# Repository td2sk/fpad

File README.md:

# fpad KiCAD data

## Features

- Key switch (Cherry MX compatible) x16
- Rotary Encoder - Illuminated (RGB) x5
- JoyStick x1
- Display
- QMK Firmware (TODO)

## License

- MIT License

## Files

- fpad7.kicad_pcb: main board
- fpad_bottom.kicad_pcb: bottom plate
- fpad_top.kicad_pcb: top plate

## Versions

- latest (recommended)
  - in root directory
- rev1 (deprecated)
  - in [releases/rev1](releases/rev1)
  - [errata](releases/rev1/errata.md)

## BOM

| Component                             | Label        | LCSC     | remarks                                                     |
| ------------------------------------- | ------------ | -------- | ----------------------------------------------------------- |
| Capacitor 0.1u 0402                   | C1           | C307331  |                                                             |
| 1N4148WS Diode SOD-323 x 16           | D1 ~ D16     | C2128    |                                                             |
| SK6812MINI-E LED x 16                 | LED1 ~ LED16 | C5149201 |                                                             |
| SSD1306 OLED Display                  | OL1          |          |                                                             |
| Register 7.5kΩ 0402                   | R1           | C25918   |                                                             |
| Register 100kΩ 3216                   | R2           | C17900   |                                                             |
| Register 10kΩ 0402 x2                 | R3, R4       | C25744   |                                                             |
| Register 3.3kΩ 0402 x2                | R5, R6       | C25890   |                                                             |
| Rotary Encoder - Illuminated (RGB) x5 | S1 ~ S5      |          | https://www.sparkfun.com/products/15141                     |
| RKJXV122400R JoyStick                 | S6           |          | https://tech.alpsalpine.com/j/products/detail/RKJXV122400R/ |
| Kailh Switch Socket x16               | SW1 ~ SW16   | C2803348 | CherryMX Compatible                                         |
| Tactile Switch                        | SW17         |          | reset button for ProMicro                                   |
| Arduino ProMicro                      | U1           |          |                                                             |
| XL9555 I/O Expander                   | U2           | C609791  |                                                             |
| IS31FL3208A LED Driver                | U3           | C2940551 |                                                             |

## Issues

- [rev1/errata.md](releases/rev1/errata.md)

## External files

### 3D CONTENTCENTRAL

The following 3D models are obtained from [3D CONTENTCENTRAL](https://www.3dcontentcentral.com/).
They are not included in this repository due to license, so please obtain them on your own and place them in the following paths.

- [Keycap](https://www.3dcontentcentral.com/secure/download-model.aspx?catalogid=171&id=941483)
  - external/3dcontentcentral/Mx_Keycap.step
- [JoyStick](https://www.3dcontentcentral.com/secure/download-model.aspx?catalogid=171&id=1681961)
  - external/3dcontentcentral/User Library-RKJXV122400R.step
- [RotaryEncoder](https://www.3dcontentcentral.com/download-model.aspx?catalogid=171&id=630216)
  - external/3dcontentcentral/User Library-Rotary Encoder v21.STEP

### SnapEDA

SnapEDA files are provided under this license as described in the following [FAQ - SnapEDA](https://www.snapeda.com/about/FAQ/).

### kbd, SparkFun-KiCAD-Libraries

Comply with the original license

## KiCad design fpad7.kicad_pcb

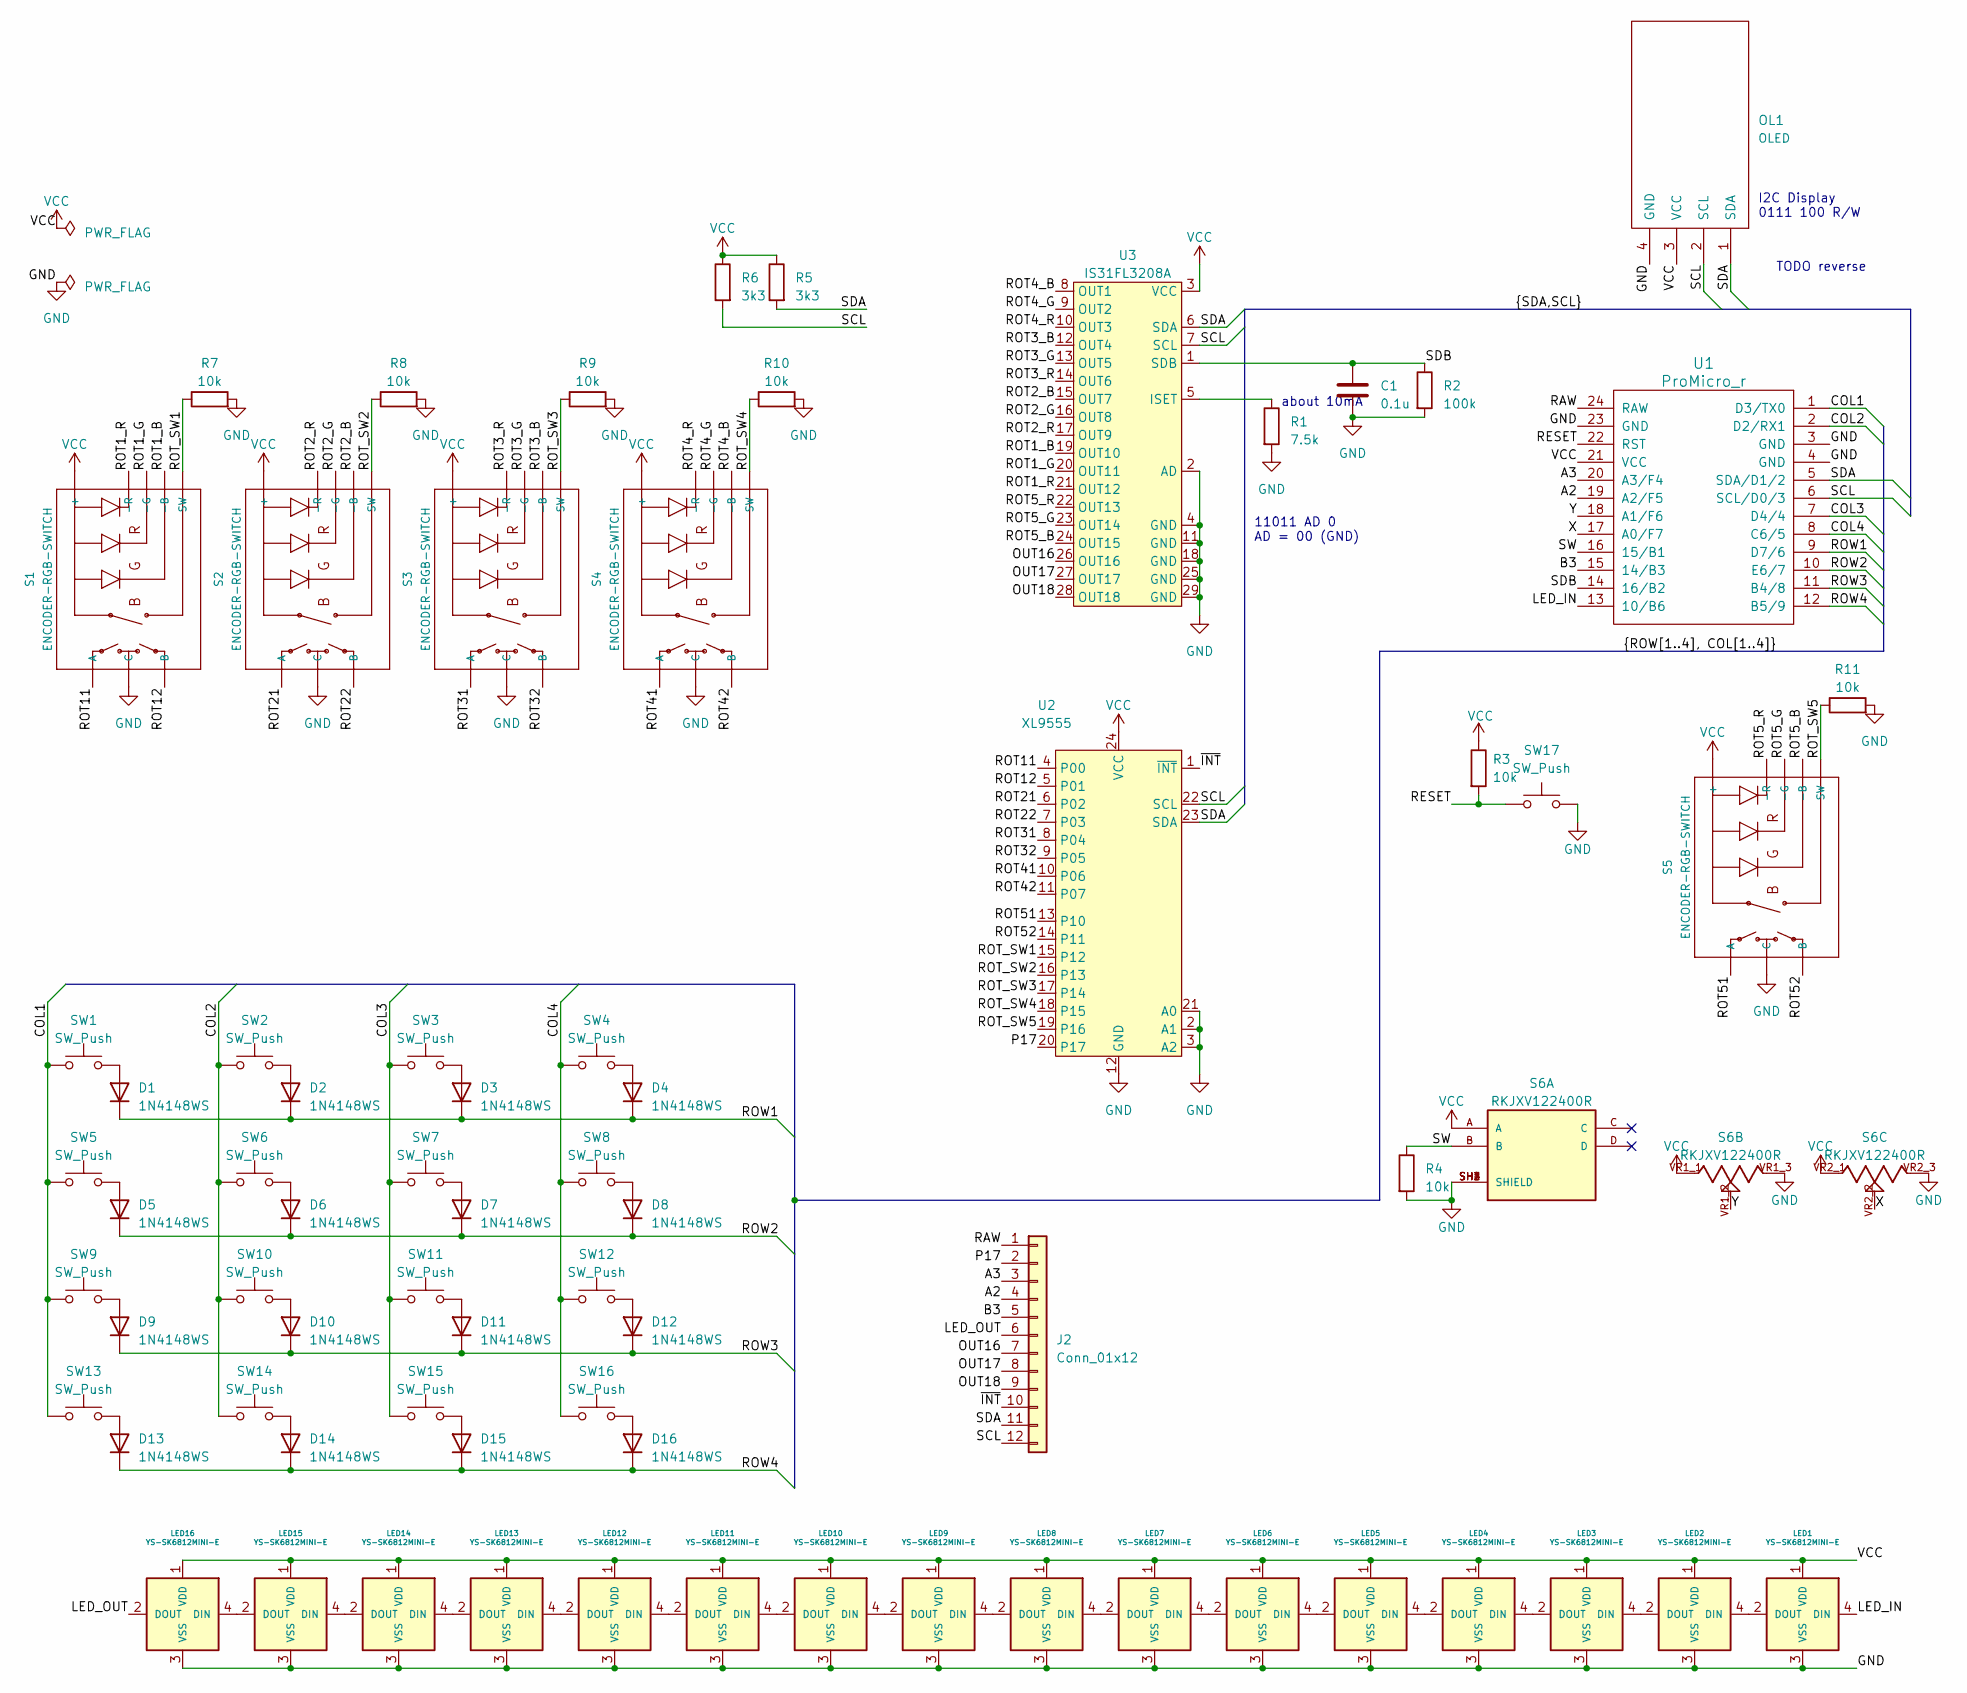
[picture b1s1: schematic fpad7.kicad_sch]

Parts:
C1: 0.1u; C_0402_1005Metric; LCSC C307331
D1, D2, D3, D4, D5, D6, D7, D8, D9, D10, D11, D12, D13, D14, D15, D16: 1N4148WS; D_SOD-323; LCSC C2128
J2: Conn_01x12; PinHeader_1x12_P1.27mm_Vertical
LED1, LED2, LED3, LED4, LED5, LED6, LED7, LED8, LED9, LED10, LED11, LED12, LED13, LED14, LED15, LED16: YS-SK6812MINI-E
OL1: OLED; OLED_v2
R1: 7.5k; R_0402_1005Metric; LCSC C25918
R2: 100k; R_1206_3216Metric; LCSC C17900
R3, R4, R7, R8, R9, R10, R11: 10k; R_0402_1005Metric; LCSC C25744
R5, R6: 3k3; R_0402_1005Metric; LCSC C25890
S1, S2, S3, S4, S5: ENCODER-RGB-SWITCH; ENCODER_LED_3
S6: RKJXV122400R; SW_RKJXV122400R; PARTREV N/A
SW1, SW2, SW3, SW4, SW5, SW6, SW7, SW8, SW9, SW10, SW11, SW12, SW13, SW14, SW15, SW16: SW_Push; CherryMX_Hotswap
SW17: SW_Push; SW_PUSH_6mm_H5mm
U1: ProMicro_r; ProMicro_v3
U2: XL9555; SSOP-24_5.3x8.2mm_P0.65mm; LCSC C609791
U3: IS31FL3208A; QFN-28-1EP_4x4mm_P0.4mm_EP2.4x2.4mm; LCSC C2940551

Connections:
/A2: J2.4, U1.19 (A2/F5)
/A3: J2.3, U1.20 (A3/F4)
/B3: J2.5, U1.15 (14/B3)
/COL1: SW1.1, SW5.1, SW9.1, SW13.1, U1.1 (D3/TX0)
/COL2: SW2.1, SW6.1, SW10.1, SW14.1, U1.2 (D2/RX1)
/COL3: SW3.1, SW7.1, SW11.1, SW15.1, U1.7 (D4/4)
/COL4: SW4.1, SW8.1, SW12.1, SW16.1, U1.8 (C6/5)
/LED_IN: LED1.4 (DIN), U1.13 (10/B6)
/LED_OUT: J2.6, LED16.2 (DOUT)
/OUT16: J2.7, U3.26 (OUT16)
/OUT17: J2.8, U3.27 (OUT17)
/OUT18: J2.9, U3.28 (OUT18)
/P17: J2.2, U2.20 (P17)
/RAW: J2.1, U1.24 (RAW)
/RESET: R3.2, SW17.1, U1.22 (RST)
/ROT1_B: S1.4 (-B), U3.19 (OUT10)
/ROT1_G: S1.2 (-G), U3.20 (OUT11)
/ROT1_R: S1.1 (-R), U3.21 (OUT12)
/ROT2_B: S2.4 (-B), U3.15 (OUT7)
/ROT2_G: S2.2 (-G), U3.16 (OUT8)
/ROT2_R: S2.1 (-R), U3.17 (OUT9)
/ROT3_B: S3.4 (-B), U3.12 (OUT4)
/ROT3_G: S3.2 (-G), U3.13 (OUT5)
/ROT3_R: S3.1 (-R), U3.14 (OUT6)
/ROT4_B: S4.4 (-B), U3.8 (OUT1)
/ROT4_G: S4.2 (-G), U3.9 (OUT2)
/ROT4_R: S4.1 (-R), U3.10 (OUT3)
/ROT5_B: S5.4 (-B), U3.24 (OUT15)
/ROT5_G: S5.2 (-G), U3.23 (OUT14)
/ROT5_R: S5.1 (-R), U3.22 (OUT13)
/ROT11: S1.A, U2.4 (P00)
/ROT12: S1.B, U2.5 (P01)
/ROT21: S2.A, U2.6 (P02)
/ROT22: S2.B, U2.7 (P03)
/ROT31: S3.A, U2.8 (P04)
/ROT32: S3.B, U2.9 (P05)
/ROT41: S4.A, U2.10 (P06)
/ROT42: S4.B, U2.11 (P07)
/ROT51: S5.A, U2.13 (P10)
/ROT52: S5.B, U2.14 (P11)
/ROT_SW1: R7.1, S1.3 (SW), U2.15 (P12)
/ROT_SW2: R8.1, S2.3 (SW), U2.16 (P13)
/ROT_SW3: R9.1, S3.3 (SW), U2.17 (P14)
/ROT_SW4: R10.1, S4.3 (SW), U2.18 (P15)
/ROT_SW5: R11.1, S5.3 (SW), U2.19 (P16)
/ROW1: D1.1 (K), D2.1 (K), D3.1 (K), D4.1 (K), U1.9 (D7/6)
/ROW2: D5.1 (K), D6.1 (K), D7.1 (K), D8.1 (K), U1.10 (E6/7)
/ROW3: D9.1 (K), D10.1 (K), D11.1 (K), D12.1 (K), U1.11 (B4/8)
/ROW4: D13.1 (K), D14.1 (K), D15.1 (K), D16.1 (K), U1.12 (B5/9)
/SCL: J2.12, OL1.2 (SCL), R6.2, U1.6 (SCL/D0/3), U2.22 (SCL), U3.7 (SCL)
/SDA: J2.11, OL1.1 (SDA), R5.2, U1.5 (SDA/D1/2), U2.23 (SDA), U3.6 (SDA)
/SDB: C1.1, R2.1, U1.14 (16/B2), U3.1 (SDB)
/SW: R4.1, S6.B, U1.16 (15/B1)
/X: S6.VR2_2, U1.17 (A0/F7)
/Y: S6.VR1_2, U1.18 (A1/F6)
/~INT: J2.10, U2.1 (~INT)
GND: C1.2, LED1.3 (VSS), LED2.3 (VSS), LED3.3 (VSS), LED4.3 (VSS), LED5.3 (VSS), LED6.3 (VSS), LED7.3 (VSS), LED8.3 (VSS), LED9.3 (VSS), LED10.3 (VSS), LED11.3 (VSS), LED12.3 (VSS), LED13.3 (VSS), LED14.3 (VSS), LED15.3 (VSS), LED16.3 (VSS), OL1.4 (GND), R1.2, R2.2, R4.2, R7.2, R8.2, R9.2, R10.2, R11.2, S1.C, S2.C, S3.C, S4.C, S5.C, S6.SH1 (SHIELD), S6.SH2 (SHIELD), S6.SH3 (SHIELD), S6.SH4 (SHIELD), S6.VR1_3, S6.VR2_3, SW17.2, U1.3 (GND), U1.4 (GND), U1.23 (GND), U2.2 (A1), U2.3 (A2), U2.12 (GND), U2.21 (A0), U3.2 (AD), U3.4 (GND), U3.11 (GND), U3.18 (GND), U3.25 (GND), U3.29 (GND)
unnamed: D1.2 (A), SW1.2
unnamed: D2.2 (A), SW2.2
unnamed: D3.2 (A), SW3.2
unnamed: D4.2 (A), SW4.2
unnamed: D5.2 (A), SW5.2
unnamed: D6.2 (A), SW6.2
unnamed: D7.2 (A), SW7.2
unnamed: D8.2 (A), SW8.2
unnamed: D9.2 (A), SW9.2
unnamed: D10.2 (A), SW10.2
unnamed: D11.2 (A), SW11.2
unnamed: D12.2 (A), SW12.2
unnamed: D13.2 (A), SW13.2
unnamed: D14.2 (A), SW14.2
unnamed: D15.2 (A), SW15.2
unnamed: D16.2 (A), SW16.2
unnamed: LED1.2 (DOUT), LED2.4 (DIN)
unnamed: LED2.2 (DOUT), LED3.4 (DIN)
unnamed: LED3.2 (DOUT), LED4.4 (DIN)
unnamed: LED4.2 (DOUT), LED5.4 (DIN)
unnamed: LED5.2 (DOUT), LED6.4 (DIN)
unnamed: LED6.2 (DOUT), LED7.4 (DIN)
unnamed: LED7.2 (DOUT), LED8.4 (DIN)
unnamed: LED8.2 (DOUT), LED9.4 (DIN)
unnamed: LED9.2 (DOUT), LED10.4 (DIN)
unnamed: LED10.2 (DOUT), LED11.4 (DIN)
unnamed: LED11.2 (DOUT), LED12.4 (DIN)
unnamed: LED12.2 (DOUT), LED13.4 (DIN)
unnamed: LED13.2 (DOUT), LED14.4 (DIN)
unnamed: LED14.2 (DOUT), LED15.4 (DIN)
unnamed: LED15.2 (DOUT), LED16.4 (DIN)
unnamed: R1.1, U3.5 (ISET)
VCC: LED1.1 (VDD), LED2.1 (VDD), LED3.1 (VDD), LED4.1 (VDD), LED5.1 (VDD), LED6.1 (VDD), LED7.1 (VDD), LED8.1 (VDD), LED9.1 (VDD), LED10.1 (VDD), LED11.1 (VDD), LED12.1 (VDD), LED13.1 (VDD), LED14.1 (VDD), LED15.1 (VDD), LED16.1 (VDD), OL1.3 (VCC), R3.1, R5.1, R6.1, S1.5 (+), S2.5 (+), S3.5 (+), S4.5 (+), S5.5 (+), S6.A, S6.VR1_1, S6.VR2_1, U1.21 (VCC), U2.24 (VCC), U3.3 (VCC)

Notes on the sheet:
TODO reverse
about 10mA
I2C Display 0111 100 R/W
11011 AD 0 AD = 00 (GND)

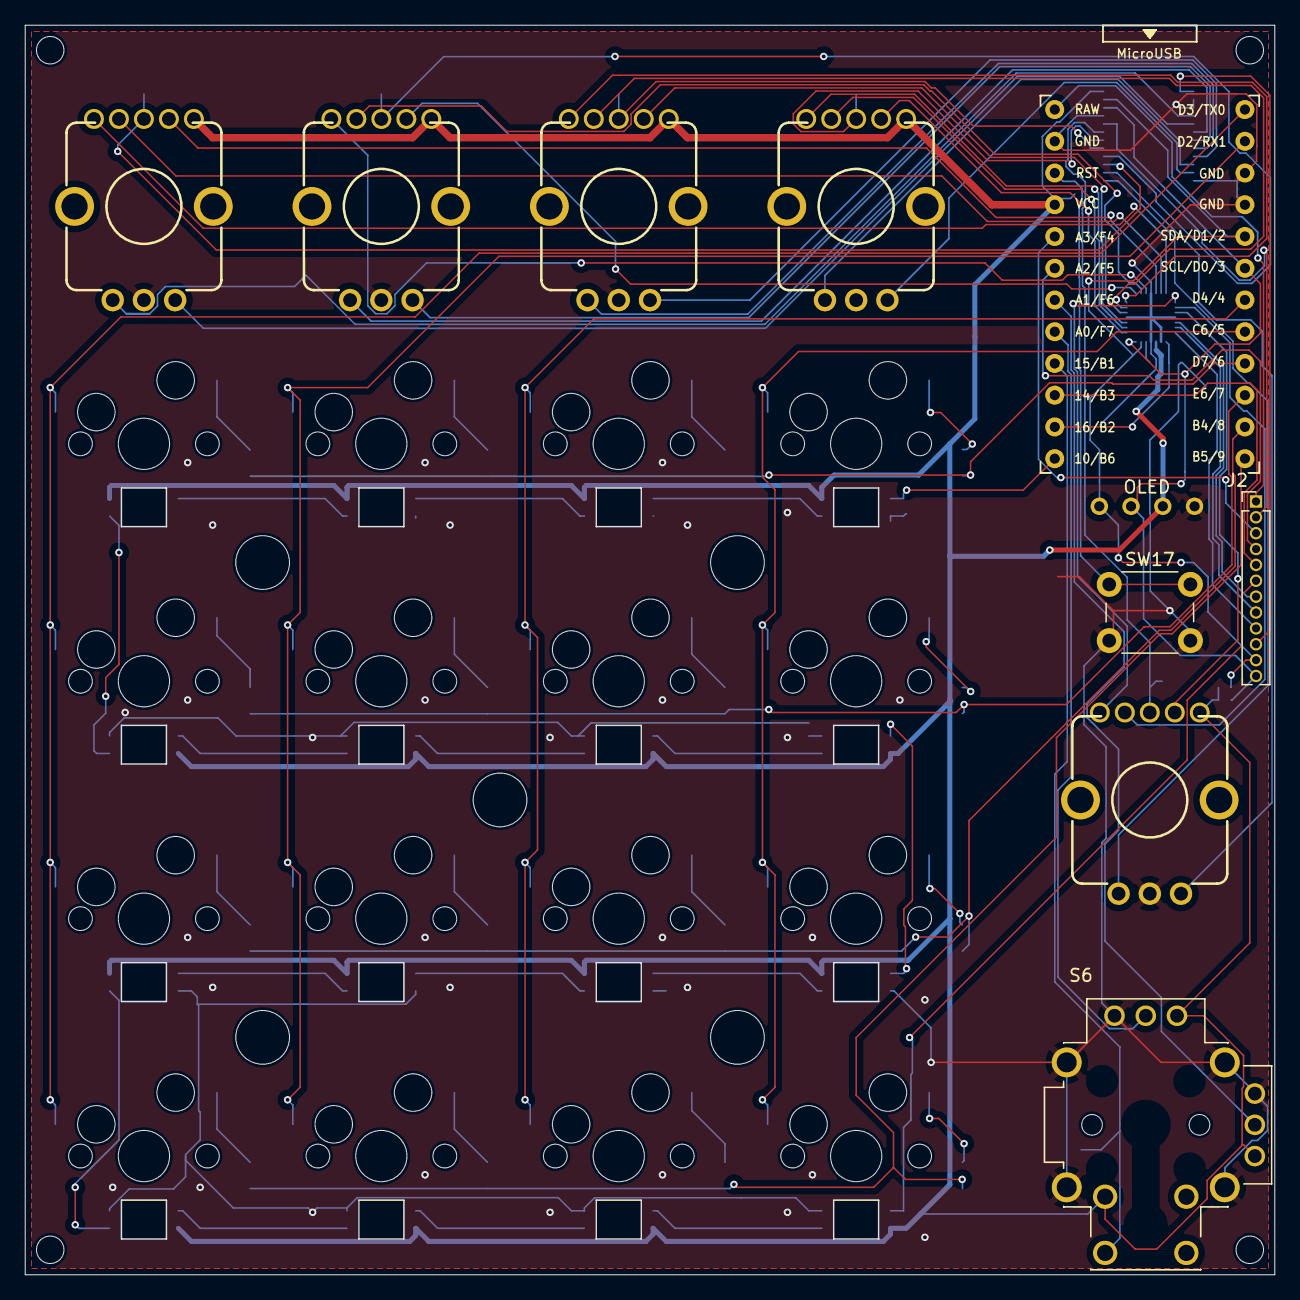
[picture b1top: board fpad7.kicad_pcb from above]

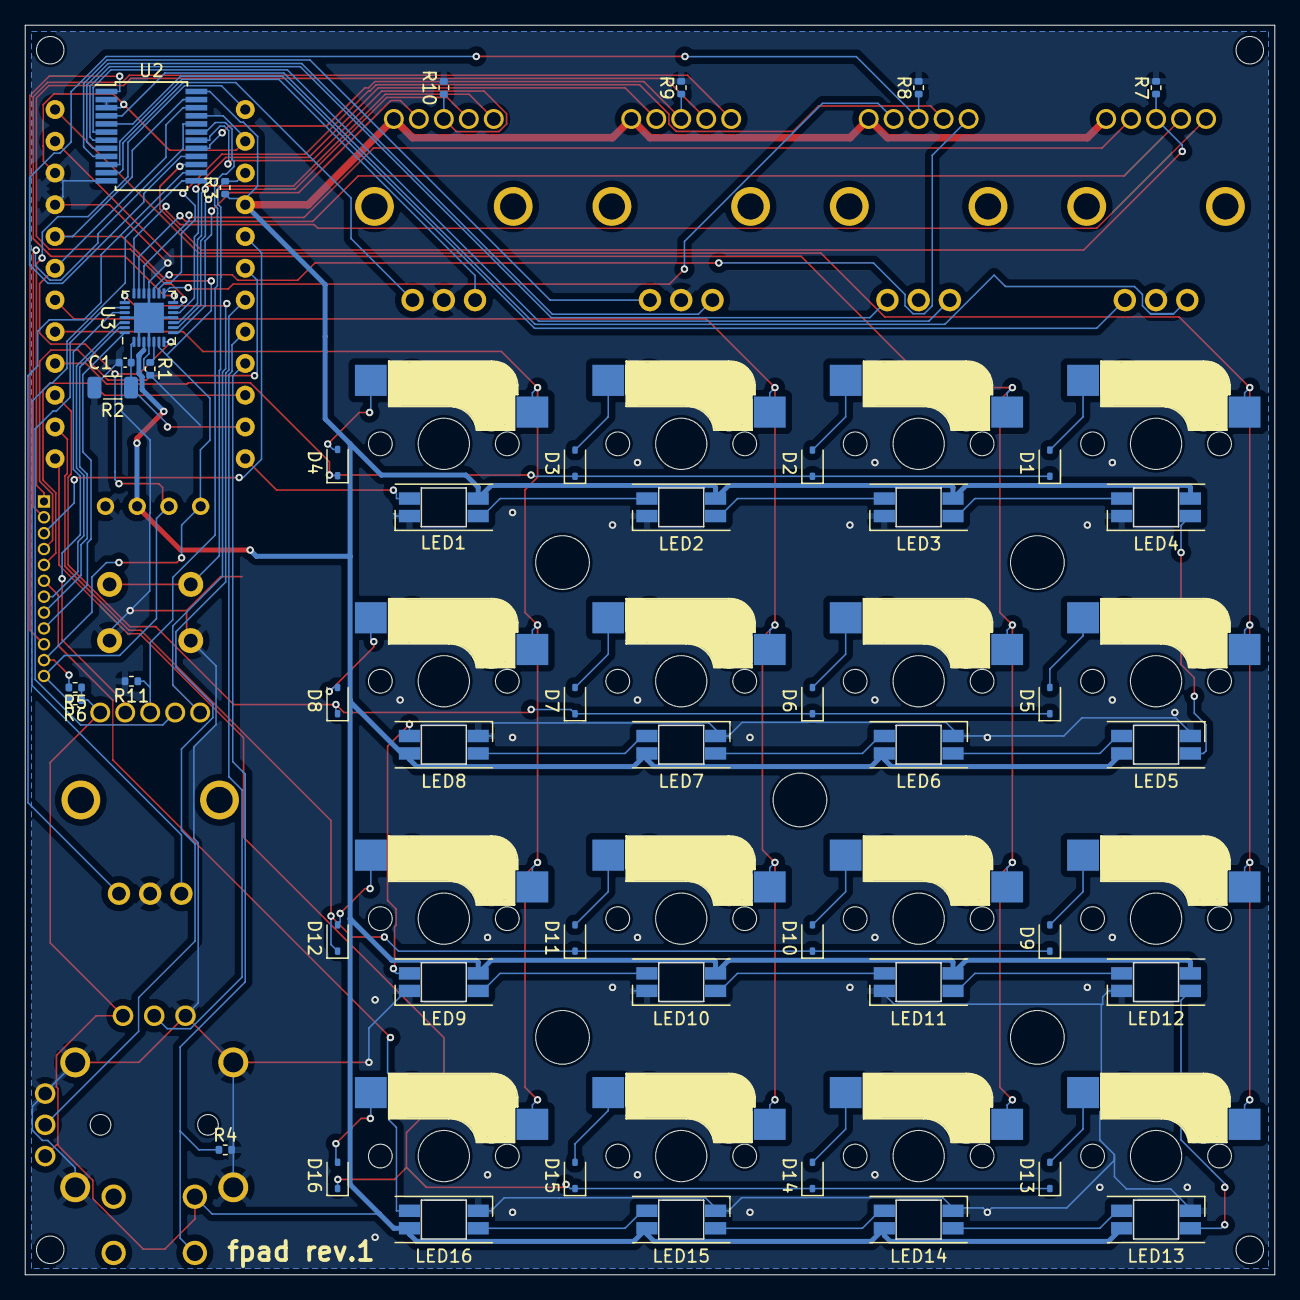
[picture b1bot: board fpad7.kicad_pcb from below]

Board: 2 copper layers, 99.9 x 99.9 mm, 72 parts (46 on the bottom side), 90 nets.

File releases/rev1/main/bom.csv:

Designator,Footprint,Quantity,Value,LCSC Part #
C1,0402,1,0.1u,C307331
"D1, D10, D11, D12, D13, D14, D15, D16, D2, D3, D4, D5, D6, D7, D8, D9",D_SOD-323,16,1N4148WS,C2128
J1,PinHeader_1x04_P2.54mm_Vertical,1,Conn_01x04,
J2,PinHeader_1x12_P1.27mm_Vertical,1,Conn_01x12,
"LED1, LED10, LED11, LED12, LED13, LED14, LED15, LED16, LED2, LED3, LED4, LED5, LED6, LED7, LED8, LED9",YS-SK6812MINI-E,16,YS-SK6812MINI-E,
R1,0402,1,7.6k,C4109
R2,1206,1,100k,C17900
R3,0402,1,10k,C25744
"S1, S2, S3, S4, S5",ENCODER_LED_3,5,ENCODER-RGB-SWITCH,
S6,SW_RKJXV122400R,1,RKJXV122400R,
"SW1, SW10, SW11, SW12, SW13, SW14, SW15, SW16, SW2, SW3, SW4, SW5, SW6, SW7, SW8, SW9",CherryMX_Hotswap,16,SW_Push,
SW17,SW_PUSH_6mm_H5mm,1,SW_Push,
U1,ProMicro_v3,1,ProMicro_r,
U2,SSOP-24_5.3x8.2mm_P0.65mm,1,XL9555,C609791
U3,QFN-28-1EP_4x4mm_P0.4mm_EP2.4x2.4mm,1,IS31FL3208A,C2940551

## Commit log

2023-02-27 add image
2023-02-28 Create LICENSE
2023-03-12 update: errata for rev1
2023-03-12 translate
2023-03-13 add BOM
2023-03-13 add firmware information
2023-03-14 fix: rot sw should be pull down
2023-03-20 update device image
2023-03-24 add via conf
